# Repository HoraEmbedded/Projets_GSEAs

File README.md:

# Projets GSEA : Horacia Azonhoumon

Élève ingénieure en Génie des Systèmes Électronique & Automatique (ENSA Tanger).
Ce dépôt regroupe mes projets académiques : systèmes embarqués, électronique, automatisme industriel et IA appliquée.

**Portfolio :** [HoraPortFolio](https://hora-portfolio.vercel.app/) · **LinkedIn :** [in/horaembedded](https://linkedin.com/in/horaembedded)

---

## Projets

### 01 · Informatique embarquée

| Projet | Description | Technologies |
|---|---|---|
| [Serre intelligente](01_Info_Embarquee/greenhouse) | Régulation climatique bare-metal pilotée par interruptions (Timer1), hystérésis à double seuil, validée en software-in-the-loop | C, ATmega2560, PlatformIO, Wokwi |
| [Machine à états finis](01_Info_Embarquee/fsm-making) | Implémentations comparées d'une FSM (switch-case vs table de transitions) avec tests unitaires Unity et analyse de complexité | C, Unity |
| [Distributeur automatique (FSM)](01_Info_Embarquee/fsm-vending-machine) | Machine à états d'un distributeur, simulée sur microcontrôleur | C, PlatformIO, Wokwi |
| [MPPT solaire](01_Info_Embarquee/mppt-solaire) | Optimisation du point de puissance maximale d'un panneau solaire — en cours | Embarqué, électronique de puissance |

### 02 · Automatique

| Projet | Description | Technologies |
|---|---|---|
| [Commande robotique](02_Automatique/commande-robotique) | Bras 2R : PID, cinématique FK/IK, trajectoires lissées (réponse ≈ 0,1 s, dépassement < 5 %) ; robot mobile en logique floue | MATLAB, Simulink, Simscape |
| [Tri convoyeur S7-1200](02_Automatique/tri-convoyeur-s7-1200) | Tri par hauteur en Ladder sur jumeau numérique Factory I/O via OPC-DA, modes Auto/Manuel/Arrêt d'urgence | TIA Portal, Factory I/O |
| [Four thermique FOPDT](02_Automatique/four-thermique-fopdt) | Identification d'un procédé FOPDT et comparaison de méthodes de réglage PID (Ziegler-Nichols, Cohen-Coon, PID Tuner) | MATLAB |
| [Robot vision & trajectoire](02_Automatique/robot-vision-trajectoire) | Suivi de trajectoire d'un robot mobile guidé par vision | Python, OpenCV, Simulink |

### 03 · Conception PCB & électronique

| Projet | Description | Technologies |
|---|---|---|
| [Driver relais NMOS](03_Conception_PCB/driver-relais-nmos) | Commande isolée de 6 relais industriels : dimensionnement, simulation, routage KiCad (Gerber), layout silicium 0,8 µm | KiCad, PSpice, Proteus, Microwind |
| [Nœud capteur IIoT LoRaWAN](03_Conception_PCB/noeud-iiot-lorawan) | Nœud capteur ultra-basse consommation avec récupération d'énergie — en cours | KiCad, LoRaWAN |

### 04 · VHDL / FPGA

En cours de formation - premiers projets à venir.

---

## Organisation

Chaque projet contient un `README.md` (problème → solution → résultats), les sources, et un dossier `docs/` (rapport, captures).

## Contact

azonhoumonhoracia@gmail.com · Tanger, Maroc

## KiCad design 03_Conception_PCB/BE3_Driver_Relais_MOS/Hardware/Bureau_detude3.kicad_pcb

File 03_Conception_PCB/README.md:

#  Interface de Commande de Puissance (Driver MOS)

## Description du projet
Ce projet a été réalisé dans le cadre du Bureau d'Étude N°3 d'Électronique de Puissance (ENSAT). Il consiste à analyser, dimensionner et concevoir une interface de commande basée sur un transistor MOS en mode commutation. 
L'objectif est de piloter de manière fiable six relais électromagnétiques (RT42405) depuis un microcontrôleur 3.3V (courant max 20 mA).

## Technologies et Outils
* **Conception PCB :** KiCad
* **Simulation & Layout Intégré :** Pspice, Microwind 
* **Composants majeurs :** * Transistor NMOS Logic-Level (IRLML2502) en boîtier SOT-23
  * Isolation par Optocoupleur (PC817) 
  * Diode de Roue Libre Schottky (1N5819HW)

##  Structure du dépôt
* `/Docs` : Rapport complet de l'étude (Calculs théoriques, dimensionnement thermique, industrialisation)
* `/Hardware` : Fichiers sources KiCad (Schématique et Routage).

## Caractéristiques techniques
* **Tension de commande :** 3.3 V 
* **Tension de puissance :** 5 V (Bobine relais)
* **Courant nominal :** ~80 mA par canal 
* **Protection :** Isolation galvanique totale de l'étage logique

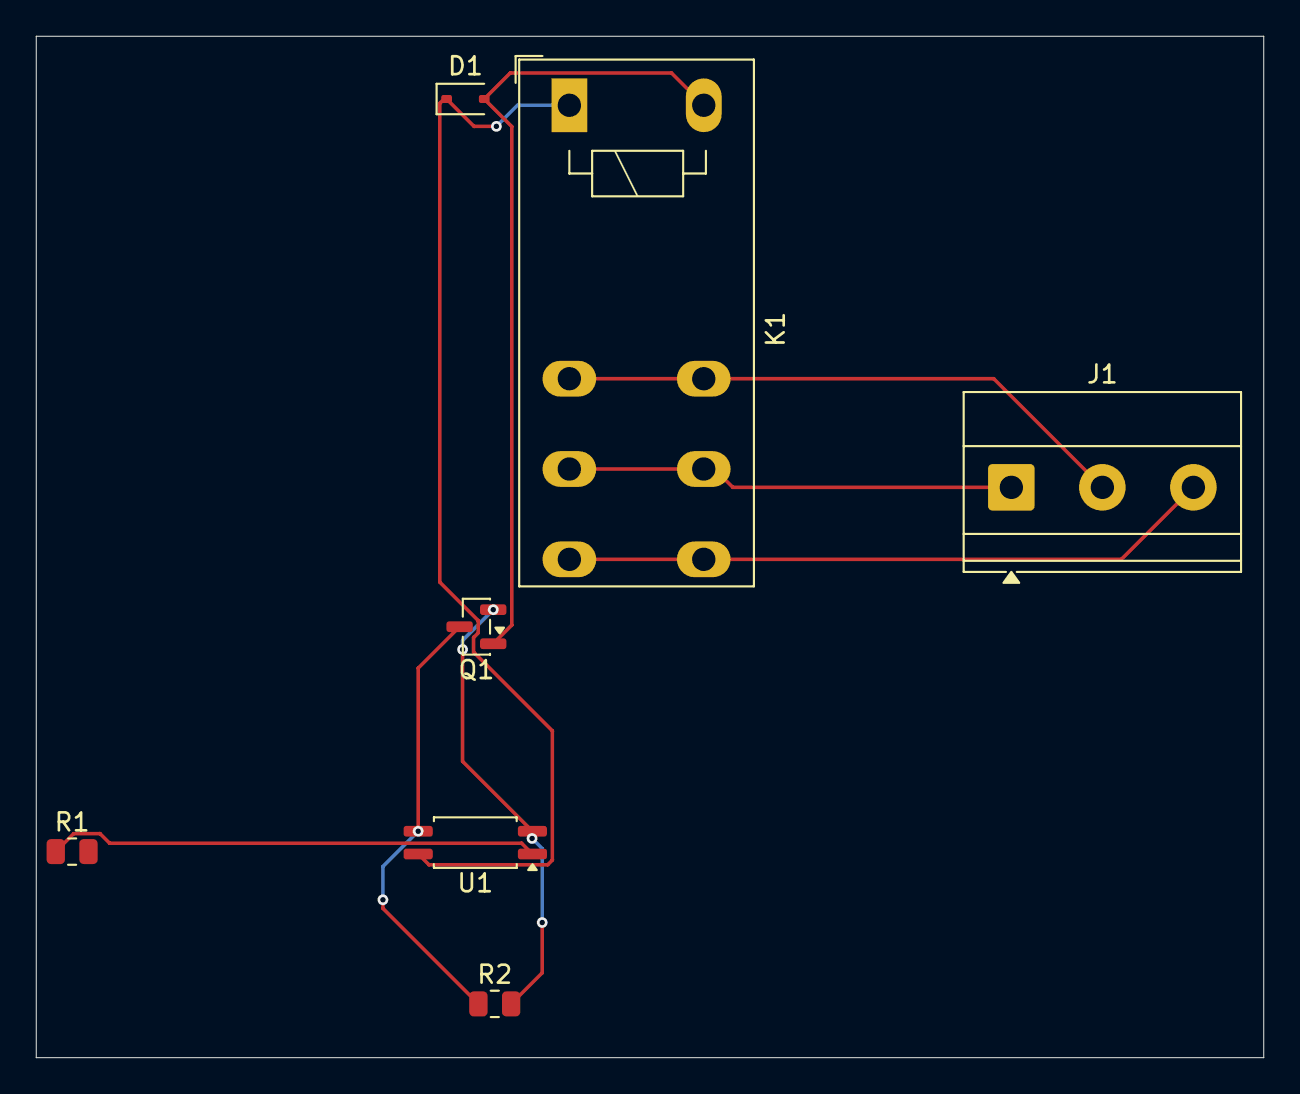
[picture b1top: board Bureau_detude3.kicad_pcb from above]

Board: 2 copper layers, 68.5 x 57.0 mm, 7 parts (0 on the bottom side), 8 nets.

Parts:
D1: 1N4148W; D_SOD-323
J1: Screw_Terminal_01x03; TerminalBlock_Phoenix_MKDS-1,5-3-5.08_1x03_P5.08mm_Horizont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
K1: Relay_SPDT; Relay_SPDT_Schrack-RT1-16A-FormC_RM5mm
Q1: Q_NMOS_DSG; SOT-23
R1, R2: R; R_0805_2012Metric
U1: PC817; SOP-4_4.4x2.6mm_P1.27mm

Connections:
+5V: D1.1 (K), K1.A1, U1.4
GND: Q1.2 (S), R2.2, U1.2
unnamed: D1.2 (A), K1.A2, Q1.1 (D)
unnamed: J1.1, K1.11
unnamed: J1.2, K1.12
unnamed: J1.3, K1.14
unnamed: Q1.3 (G), R2.1, U1.3
unnamed: R1.1, U1.1

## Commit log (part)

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2026-05-25 Create .gitignore
    add gitignore
2026-05-25 Create Rapport_Bureau_Etude_3.pdf
    Ajout du BE3 : Étude et dimensionnement Driver de Relais MOS
2026-05-25 hardware files
    update hardware files
2026-05-25 update
    Update report and hardware
2026-05-25 Create LatexFichier.zip
    add latex files
2026-05-25 Create README.md
    add README
2026-05-25 README
    Ajout structuré du BE3 complet avec routage KiCad et README
2026-05-25 Update README.md
    Update
2026-05-25 View
    Ajout du dossier Images et de la vue 3D dans le README
2026-05-26 Project
    chore: initialisation du projet de serre intelligente avec PlatformIO
2026-05-26 update
    update diagram.json
2026-05-26 Create wokwi.toml
    add wokwi.toml
2026-05-26 simulation
    simulation code
2026-05-26 Update main.c
    implementation du driver UART en bare-metal
2026-05-26 Update main.c
    allumer les led
2026-05-26 Update main.c
    implementation du pilote TWI/I2C et controle de l'ecran LCD
2026-05-26 update
    update simulation platformIO file
2026-05-26 Update main.c
    simulaltion update
2026-05-26 Update main.c
    intégrer fonction relai avec hystérésis dans le fonction pour éviter l'endommagement du matériel physique
2026-05-26 Update main.c
    add interruption + timer
2026-05-26 Update main.c
    Doxygen commentaires
2026-05-28 Update main.c
    update code in english
2026-05-29 Create index.html
    myPortofolio
2026-05-29 Update index.html
    update
2026-05-29 Update index.html
    auto-update
2026-05-29 Update index.html
    auto-update portfolio
2026-05-29 update
    auto-update portfolio
2026-05-29 CV ajout
    ajout de mon CV
2026-05-29 auto-update
    update Mon portfolio
2026-05-29 update
    auto
2026-05-30 Update
    update portfolio and cv files
2026-05-30 Add detailed README for intelligent greenhouse system
    Added a comprehensive README.md detailing the project, features, hardware architecture, software architecture, installation instructions, and author information.
2026-05-30 Simplify README by removing unnecessary content
    Removed detailed instructions and author section from README.
2026-05-30 Update README with simulation validation details
    Ajout d'une section sur la validation par simulation et mise à jour de la description du projet pour inclure des détails sur la simulation dans Wokwi.
2026-05-30 Refine README formatting and content clarity
    Corrected formatting and improved clarity in the README.
2026-05-30 Add image to README for Serre Intelligente
    Added an image to the README for visual reference.
2026-05-30 Replace local image with hosted image in README
    Updated image reference in README with a hosted image URL.
2026-05-30 Update image in README.md with new source and alt text
    Updated image source in README and added alt text.
2026-05-31 update
    update
2026-05-31 update
    update portfolio
2026-06-04 update
    Various improvements and updates
2026-06-05 update
    change name serre intelligente to Greenhouse
2026-06-06 Create README.md
    feat: initial commit with project setup and readme
2026-06-06 Create fsm.c
    feat: implement version 1 of FSM using switch-case
2026-06-06 Update fsm.c
    feat: implement version 1 of FSM using switch-case logic
2026-06-06 update
    feat: implement version 1 of FSM using switch-case logic
2026-06-06 update
    refactor: replace switch-case FSM with scalable transition
2026-06-06 Update fsm(transition).c
    feat: add 30s timeout and UART message to SELECTION state
2026-06-06 Create fsmFV.h
    refactor Final Version: replace switch-case FSM with scalable transition
2026-06-06 feat
    feat: complete FSM implementation, Unity test suite, and Doxygen
2026-06-06 docs
    docs: add comprehensive project README
2026-06-07 config
    config: Configuration de la carte STM32 Nucleo-C031C6 pour PlatformIO et Wokwi
2026-06-07 Update main.c
    feat: FSM V1 fonctionnelle avec switch-case
2026-06-07 update
    config : platformIO, wokwi
2026-06-07 Create main.c
    feat : main
2026-06-07 update
    config main.c
2026-06-07 delete
    update
2026-06-08 config
    config : range projects
2026-06-08 config
    config projects
2026-06-09 initial commit
    Initial commit - Création du projet PlatformIO
2026-06-09 config
    config : diagram.json
2026-06-09 initial commit
    Initial commit: Création du projet FSM STM32Cube
2026-06-09 config
    Ajout de la configuration Wokwi et de la carte STM32 virtuelle
2026-06-09 Config
    Ajout de la configuration Wokwi et de la carte STM32
2026-06-10 Update main.c
    update
2026-06-10 configuration
    feat : fsm.h
2026-06-10 update
    Implémentation de la Loop while et test bouton
2026-06-11 Config
    feat : Ajout des tests unitaires et de la documentation Doxygen
2026-06-11 feat
    Feat : Files to display the menu of FSM in OLED screen
2026-06-15 Create README
    docs: add initial project README
2026-06-15 Create process_identification.m
    feat: create script for process identification
2026-06-15 Update process_identification.m
    feat: implement virtual oven simulation for 10 percent step response
2026-06-15 Update README
    docs: add comprehensive FOPDT parameter identification report
2026-06-15 docs
    add readme
2026-06-15 Create pid_tuning_zn.m
    feat: implement Ziegler-Nichols PID tuning and closed-loop simulation
2026-06-15 Create pid_tuning_cc.m
    feat: implement Cohen-Coon PID tuning for better setpoint tracking
2026-06-16 feat
    feat: implement final comparison script with disturbance robustness test
2026-06-20 Create README.md
    Initial commit: Set up project directory structure and README
2026-06-20 Create init_robot_params.m
    feat: Add initialization script for robot kinematic parameters
2026-06-20 Create MobileRobot_Simulation.slx
    feat: Add RobotModel subsystem with kinematic equations and integrators
2026-06-20 feat: Implement ControllerBlock with dual PID regulators and wheel speed calculation
    feat: Implement ControllerBlock with dual PID regulators and wheel speed calculation
2026-06-20 Update MobileRobot_Simulation.slx
    feat: Implement VisionBlock for image processing and tracking error calculation
2026-06-20 Update MobileRobot_Simulation.slx
    feat: Implement SimCam module and connect all subsystems in a closed loop
2026-06-21 feat: Add vision script to extract waypoints from PNG trajectory
    feat: Add vision script to extract waypoints from PNG trajectory
2026-06-21 Create trajectory_tracking_model.slx
    feat: Initialize Simulink model and add Differential Drive block
2026-06-21 Update trajectory_tracking_model.slx
    feat: Add Pure Pursuit controller and establish closed-loop with the robot
2026-06-21 Update trajectory_tracking_model.slx
    fix: Add Integrator block for state calculation and setup workspace export
2026-06-21 Create main_sim.m
    feat: Add main script to initialize variables, run simulation, and plot performance
2026-06-21 Update trajectory_tracking_model.slx
    feat: Add main script to initialize variables, run simulation, and plot performance
2026-06-21 fix: Add nearest neighbor sorting and downsampling to generate sequential waypoints
    fix: Add nearest neighbor sorting and downsampling to generate sequential waypoints
2026-06-21 Create create_env.m
    feat: Generate 2D occupancy map with an obstacle blocking the trajectory
2026-06-21 Update main_sim.m
    feat: Add environment loading and implement distance sensor in Simulink via MATLAB Function
2026-06-21 Update trajectory_tracking_model.slx
    feat: Add Stateflow chart for obstacle detection and emergency avoidance logic
2026-06-22 feat: Add environment loading and implement distance sensor in Simulink via MATLAB Function
    feat: Add environment loading and implement distance sensor in Simulink via MATLAB Function
